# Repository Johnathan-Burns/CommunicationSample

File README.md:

# ATMEGA328PB-AU Communication Sample Board
## Designed by Johnathan Burns

---

This project is a custom designed prototype with several external serial connectors.

These include:
- 2x SPI Connections
- 2x I2C Connections
- 1x UART Connection
- 1x ICSP Connection (Signals shared with SPI\_CONN\_0)

---

This board is useful when a large amount of serial connectivity is required in a relatively small space. There are several unused pins on the ATMEGA328PB that could be used for additional GPIO connectivity, but this was not required by the design specifications.

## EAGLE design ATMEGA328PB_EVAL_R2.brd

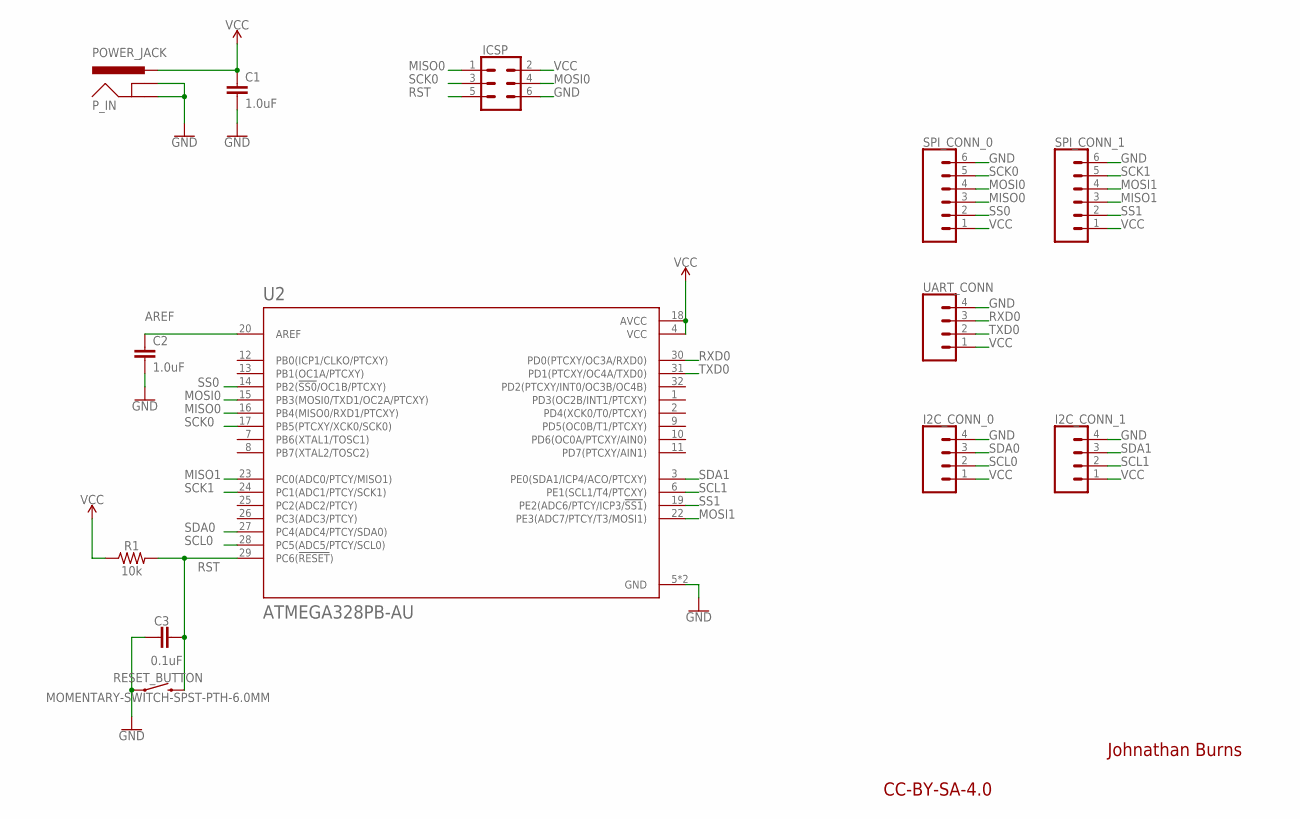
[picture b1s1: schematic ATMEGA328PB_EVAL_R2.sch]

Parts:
C1, C2: 1.0uF; 0603
C3: 0.1uF; 0603
I2C_CONN_0, I2C_CONN_1: CONN_04; 1X04
ICSP: CONN_03X2NO_SILK; 2X3-NS
P_IN: POWER_JACK; POWER_JACK_PTH
R1: 10k; 0603
RESET_BUTTON: MOMENTARY-SWITCH-SPST-PTH-6.0MM; TACTILE_SWITCH_PTH_6.0MM
SPI_CONN_0, SPI_CONN_1: CONN_06SILK_FEMALE_PTH; 1X06
U2: ATMEGA328PB-AU; QFP80P900X900X120-32N
UART_CONN: CONN_04; 1X04

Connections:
AREF: C2.1, U2.20 (AREF)
GND: C1.2, C2.2, C3.1, I2C_CONN_0.4, I2C_CONN_1.4, ICSP.6, P_IN.GND, P_IN.GNDBREAK, RESET_BUTTON.1, SPI_CONN_0.6, SPI_CONN_1.6, U2.5 (GND), U2.21 (GND), UART_CONN.4
MISO0: ICSP.1, SPI_CONN_0.3, U2.16 (PB4(MISO0/RXD1/PTCXY))
MISO1: SPI_CONN_1.3, U2.23 (PC0(ADC0/PTCY/MISO1))
MOSI0: ICSP.4, SPI_CONN_0.4, U2.15 (PB3(MOSI0/TXD1/OC2A/PTCXY))
MOSI1: SPI_CONN_1.4, U2.22 (PE3(ADC7/PTCY/T3/MOSI1))
RST: C3.2, ICSP.5, R1.2, RESET_BUTTON.3 (2), U2.29 (PC6(!RESET!))
RXD0: U2.30 (PD0(PTCXY/OC3A/RXD0)), UART_CONN.3
SCK0: ICSP.3, SPI_CONN_0.5, U2.17 (PB5(PTCXY/XCK0/SCK0))
SCK1: SPI_CONN_1.5, U2.24 (PC1(ADC1/PTCY/SCK1))
SCL0: I2C_CONN_0.2, U2.28 (PC5(ADC5/PTCY/SCL0))
SCL1: I2C_CONN_1.2, U2.6 (PE1(SCL1/T4/PTCXY))
SDA0: I2C_CONN_0.3, U2.27 (PC4(ADC4/PTCY/SDA0))
SDA1: I2C_CONN_1.3, U2.3 (PE0(SDA1/ICP4/ACO/PTCXY))
SS0: SPI_CONN_0.2, U2.14 (PB2(!SS0!/OC1B/PTCXY))
SS1: SPI_CONN_1.2, U2.19 (PE2(ADC6/PTCY/ICP3/!SS1!))
TXD0: U2.31 (PD1(PTCXY/OC4A/TXD0)), UART_CONN.2
VCC: C1.1, I2C_CONN_0.1, I2C_CONN_1.1, ICSP.2, P_IN.PWR, R1.1, SPI_CONN_0.1, SPI_CONN_1.1, U2.4 (VCC), U2.18 (AVCC), UART_CONN.1

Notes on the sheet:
Johnathan Burns
CC-BY-SA-4.0

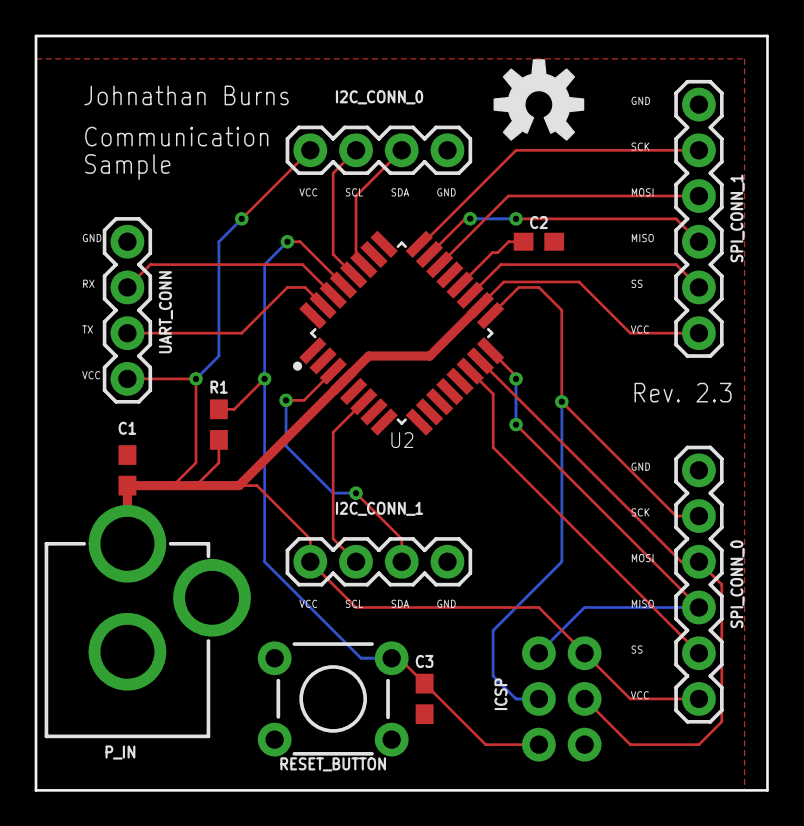
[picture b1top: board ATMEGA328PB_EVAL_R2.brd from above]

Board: 2 copper layers, 40.6 x 41.9 mm, 14 parts (0 on the bottom side), 18 nets.

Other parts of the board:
OSHW_LOGO: OSHW-LOGO-M

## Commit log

2021-06-26 Version 1 and 2.2 of my sample design
2021-06-26 Added EAGLE project file
2021-06-26 Added License and schematic PDF
2021-06-26 Added a README
2021-06-27 Enlarged main power trace(s)
2021-06-27 Cleaned up topside PDF
2021-06-28 Cleaned up directory structure

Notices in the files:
parts and their libraries:
SparkFun-Capacitors: Licensing: Creative Commons ShareAlike 4.0 International - https://creativecommons.org/licenses/by-sa/4.0
